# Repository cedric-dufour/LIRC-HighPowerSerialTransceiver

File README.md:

LIRC High-Power Serial Transceiver
==================================

This electronics project spawned from my need to blast Philips RC6 infrared
codes across my entire living room and remote control my existing Feller
Zeptrion [1] (house control) electric installation, with the help of the Linux
Infrared Remote Control (LIRC) [2].

Unfortunately, my existing USB dongle would not transmit RC6 codes while my
spare serial transmitter would lack the power to blast IR accross the entire
room.

I thus designed this High-Power Serial Transceiver with the following key
points in mind:

 1. high-power IR transmission, using an external power source such as the
    RS-232 12-volt "Power-over-System" provided by some card (e.g. Exsys
    44092-2 [3]) or using a 9-volt battery

 2. versatile IR reception, compatible with both 36/38kHz and 56kHz remotes

 3. indicator LED to monitor IR reception (and transmission)

 4. do-it-yourself using "off-the-shelf" standard components [4]

starting with the designs proposed by LIRC and its contributors:

   http://www.lirc.org/transmitters.html

   http://www.lirc.org/receivers.html

and using this opportunity to over-design some of the components, such as to
protect the high-power LEDs to be driven out of specifications by the full
range of potential RS-232 signals/voltages (using a high-pass input filter
and a two-transistors constant current source).

Provided files are:

 - KiCAD/Eeeschema schematic (and corresponding PDF plot)

 - KiCAD/PCBnew layout (and corresponding SVG export)

Please bear with me that the provided PCB layout is targeted towards 2.54mm-pad
rapid prototype boards rather than actual PCB manufacturing.

Enjoy!

References:

[1] https://www.feller.ch/de/Produktangebot/Licht-und-Storensteuerungssystem/Licht-Storensteuerung-zeptrion

[2] http://www.lirc.org

[3] http://www.exsys.de/index.php?page=product&info=202

[4] http://farnell.com

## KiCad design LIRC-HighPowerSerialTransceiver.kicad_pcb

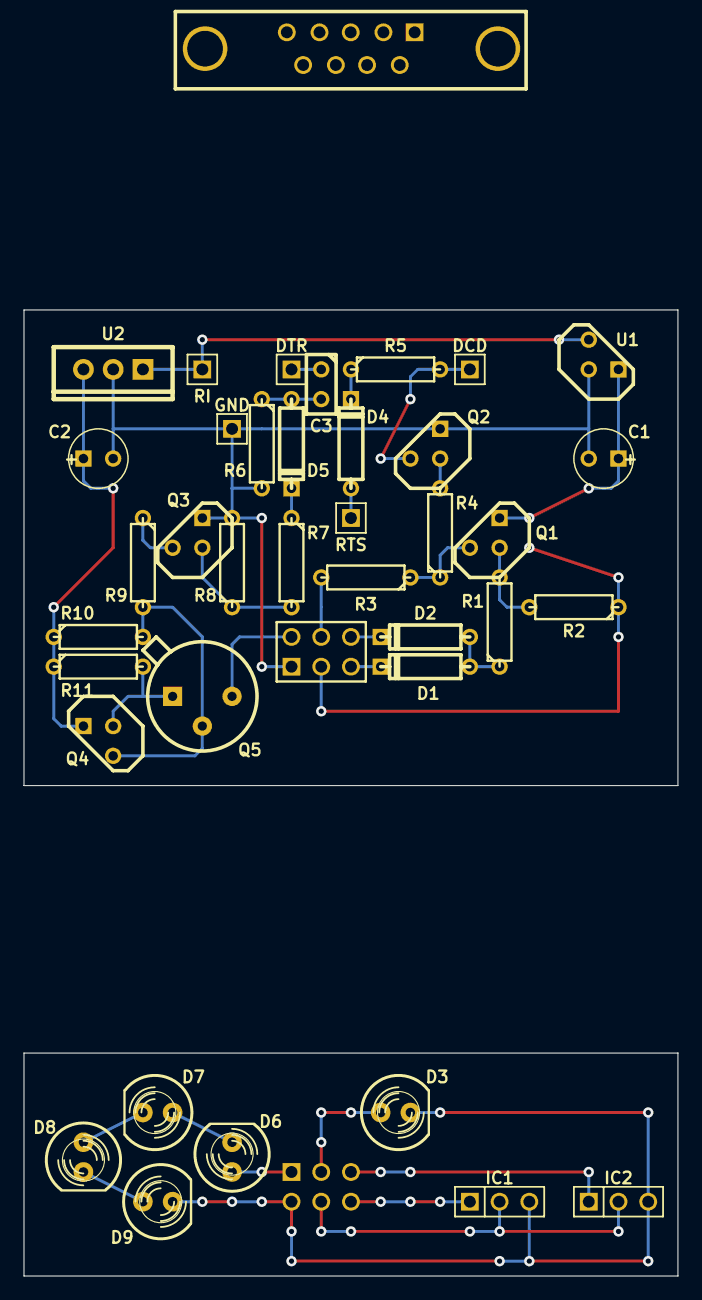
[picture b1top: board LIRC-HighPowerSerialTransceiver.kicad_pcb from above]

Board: 2 copper layers, 55.9 x 82.6 mm, 40 parts (1 on the bottom side), 25 nets.

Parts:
C1, C2: 10uF; C1V5
C3: 4.7nF; C1
D1, D2, D4, D5: 1N4148; D3
D3: LD20_RED; LED-5MM
D6: TSAL6200; LED-5MM
D7, D8, D9: LED-5MM
DCD: Val**; PIN_ARRAY_1
DTR: Val**; PIN_ARRAY_1
GND: Val**; PIN_ARRAY_1
IC1: TSOP2238; PIN_ARRAY_3X1
IC2: TSOP2256; PIN_ARRAY_3X1
J1: DB9; DB9FD
PIN_ARRAY_3X2, PIN_ARRAY_3X2#2: Val**; pin_array_3x2
Q1, Q4: 2N3906; TO92-INVERT
Q2, Q3: 2N3904; TO92-INVERT
Q5: BC161-16; TO39EBC
R1, R6, R7: 10kΩ; R3
R2, R4, R5, R8: 4.7kΩ; R3
R3: 220Ω; R3
R9: 680Ω; R3
R10: 6.8kΩ; R3
R11: 3.3Ω; R3
RI: Val**; PIN_ARRAY_1
RTS: Val**; PIN_ARRAY_1
U1: LM2936Z-5.0; TO92-INVERT
U2: LM2937ET-8.0; TO220_123_VERT

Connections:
5V: C1.1, IC1.2, IC2.2, PIN_ARRAY_3X2.4, PIN_ARRAY_3X2#2.3, Q1.1, R2.1, U1.1
8V: C2.1, Q4.1, R10.1, R11.1, U2.3
DCD: DCD.1, J1.1, Q2.3, R5.2
DTR: C3.1, DTR.1, J1.4
GND: C1.2, C2.2, D3.2, D9.2, GND.1, IC1.3, IC2.3, J1.5, PIN_ARRAY_3X2.2, PIN_ARRAY_3X2#2.1, Q2.1, Q3.1, R6.2, R8.2, U1.2, U2.2
unnamed: D7.2, D8.1
unnamed: D8.2, D9.1
unnamed: D6.2, D7.1
unnamed: Q2.2, R4.2
unnamed: Q1.3, R3.1, R4.1
unnamed: D5.2, R7.1
unnamed: Q3.3, R9.1
unnamed: C3.2, D5.1, R6.1
unnamed: D4.2, R5.1
unnamed: Q4.2, Q5.1, R11.2
unnamed: Q4.3, Q5.2, R9.2, R10.2
unnamed: D1.1, D2.1, R1.1
unnamed: Q1.2, R1.2, R2.2
unnamed: Q3.2, R7.2, R8.1
RI: J1.9, RI.1, U1.3, U2.1
RTS: D4.1, J1.7, RTS.1
RX38: D1.2, IC1.1, PIN_ARRAY_3X2.6, PIN_ARRAY_3X2#2.5
RX56: D2.2, IC2.1, PIN_ARRAY_3X2.5, PIN_ARRAY_3X2#2.6
RXLD: D3.1, PIN_ARRAY_3X2.3, PIN_ARRAY_3X2#2.4, R3.2
TXLD: D6.1, PIN_ARRAY_3X2.1, PIN_ARRAY_3X2#2.2, Q5.3

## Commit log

2016-11-22 * Post Tenebras Lux
2016-11-22 - Downsized overview image
2016-11-24 - Added project-specific components and modules libraries
